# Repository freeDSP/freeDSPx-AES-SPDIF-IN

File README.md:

# freeDSPx AES/SPDIF IN

BOARD STATUS: READY TO BE BUILT

MAIN COORDINATOR: [florian](https://github.com/FlorianPfeil)

This is a digital input add-on board based on a design found at [latent laboratories](http://www.latentlaboratories.com/dsp-01/). It's built around a CS8422 asynchronous sample rate converter, has S/PDIF and AES/EBU input plus two potentiometers, a toggle switch and a LED connected to the ADAU's GPIOs.

## Comments

* The design uses the bit clock signal of the serial output as master clock for the ASRC. Therefore, the output needs to be configured in SigmaStudio as ‚Master Mode‘. The BCLK frequency needs to be selected as ‚internal clock/4‘.

## License

This work and all other materials under https://github.com/freeDSP are licensed under a <a rel="license" href="http://creativecommons.org/licenses/by-sa/4.0/legalcode">Creative Commons Attribution Share-Alike 4.0 license</a>. This allows for both personal and commercial derivative works, as long as they credit freeDSP and release their designs under the same license.

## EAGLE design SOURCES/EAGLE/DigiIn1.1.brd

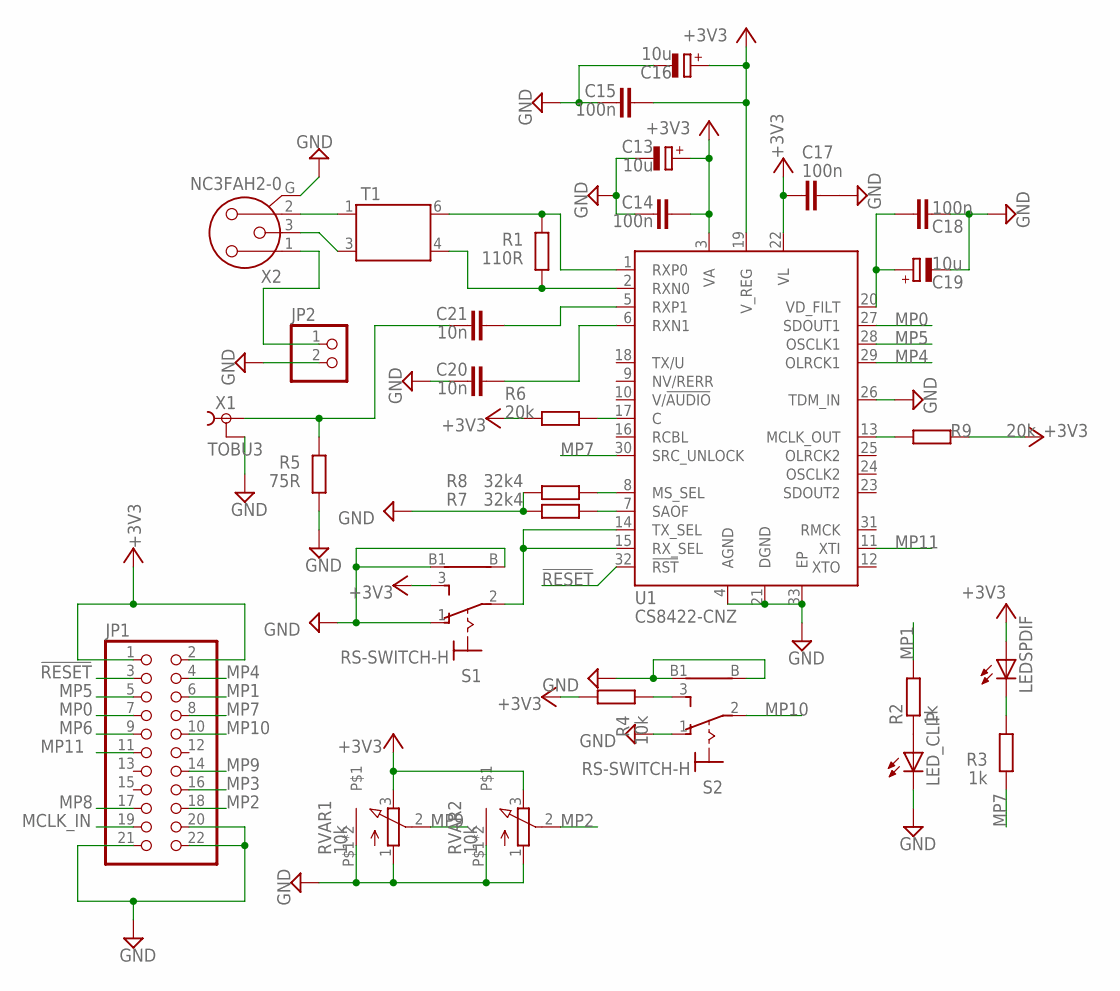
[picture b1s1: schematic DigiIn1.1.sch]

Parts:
C13, C16, C19: 10u; E2-5
C14, C15, C17, C18: 100n; C025-024X044
C20, C21: 10n; C075-032X103
JP1: PINHD-2X11; 2X11
JP2: PINHD-1X2; 1X02
LEDSPDIF: LED3MM
LED_CLIP: LED3MM
R1: 110R; 0207/10
R2, R3: 1k; 0207/10
R4: 10k; 0207/10
R5: 75R; 0207/2V
R6, R9: 20k; 0207/10
R7, R8: 32k4; 0207/10
RVAR1, RVAR2: 10k; ALPS-RK09
S1, S2: RS-SWITCH-H
T1: TRAFO_DIL6
U1: CS8422-CNZ; QFN50P500X500X100-33N
X1: TOBU3
X2: NC3FAH2-0

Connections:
!RESET!: JP1.3, U1.32 (!RST!)
+3V3: C13.+, C14.1, C15.1, C16.+, C17.1, JP1.1, JP1.2, LEDSPDIF.A, R4.2, R6.1, R9.2, RVAR1.3, RVAR2.3, S1.3, U1.3 (VA), U1.19 (V_REG), U1.22 (VL)
GND: C13.-, C14.2, C15.2, C16.-, C17.2, C18.2, C19.-, C20.2, JP1.20, JP1.21, JP1.22, JP2.2, LED_CLIP.K (C), R5.2, R7.1, R8.1, RVAR1.1, RVAR1.P$1, RVAR1.P$2, RVAR2.1, RVAR2.P$1, RVAR2.P$2, S1.1, S1.B, S1.B1, S2.1, S2.B, S2.B1, U1.4 (AGND), U1.21 (DGND), U1.26 (TDM_IN), U1.33 (EP), X1.2, X1.2@1 (2), X1.2@2 (2), X2.G
MCLK_IN: JP1.19
MP0: JP1.7, U1.27 (SDOUT1)
MP1: JP1.6, R2.2
MP2: JP1.18, RVAR2.2
MP3: JP1.16
MP4: JP1.4, U1.29 (OLRCK1)
MP5: JP1.5, U1.28 (OSCLK1)
MP6: JP1.9
MP7: JP1.8, R3.1, U1.30 (SRC_UNLOCK)
MP8: JP1.17
MP9: JP1.14, RVAR1.2
MP10: JP1.10, S2.2
MP11: JP1.11, U1.11 (XTI)
unnamed: LED_CLIP.A, R2.1
unnamed: R1.1, T1.6, U1.1 (RXP0)
unnamed: C21.2, R5.1, X1.1
unnamed: LEDSPDIF.K (C), R3.2
unnamed: R1.2, T1.4, U1.2 (RXN0)
unnamed: T1.1, X2.2
unnamed: T1.3, X2.3
unnamed: S1.2, U1.14 (TX_SEL), U1.15 (RX_SEL)
unnamed: C18.1, C19.+, U1.20 (VD_FILT)
unnamed: R4.1, S2.3
unnamed: JP2.1, X2.1
unnamed: C20.1, U1.6 (RXN1)
unnamed: C21.1, U1.5 (RXP1)
unnamed: R6.2, U1.17 (C)
unnamed: R7.2, U1.7 (SAOF)
unnamed: R8.2, U1.8 (MS_SEL)
unnamed: R9.1, U1.13 (MCLK_OUT)

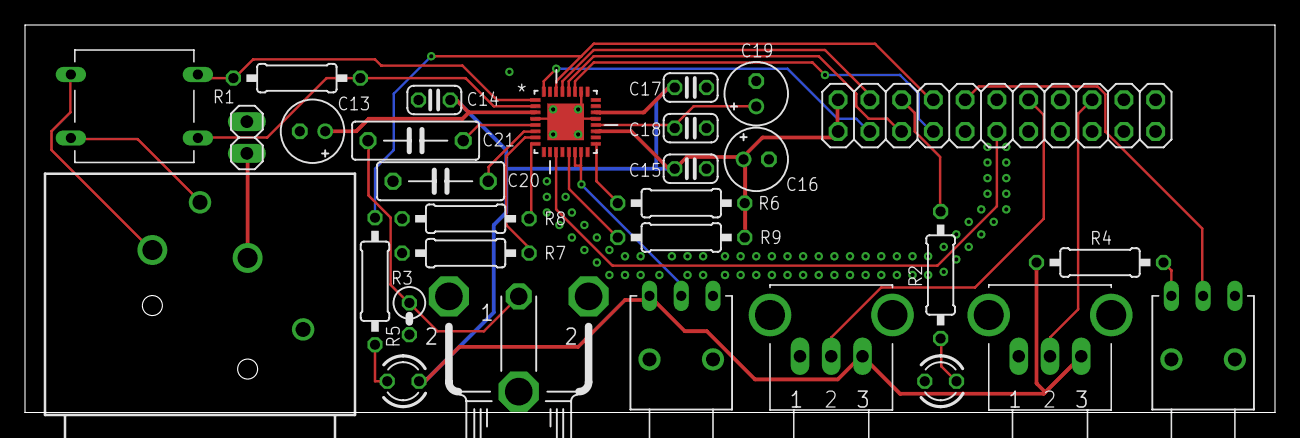
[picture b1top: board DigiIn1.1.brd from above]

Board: 2 copper layers, 100.0 x 31.0 mm, 30 parts (0 on the bottom side), 29 nets.

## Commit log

2015-12-02 folder structure + initial sources V1.1
    added basic folder structure and files from Florian
2015-12-02 added folders for gerber files
2015-12-02 folder for software example
2015-12-02 link format test
2016-01-18 2.1 XOver
    2.1 Crossover with master and sub volume, bypass switch and clip
    indicator
2016-03-04 Add link to documentation
